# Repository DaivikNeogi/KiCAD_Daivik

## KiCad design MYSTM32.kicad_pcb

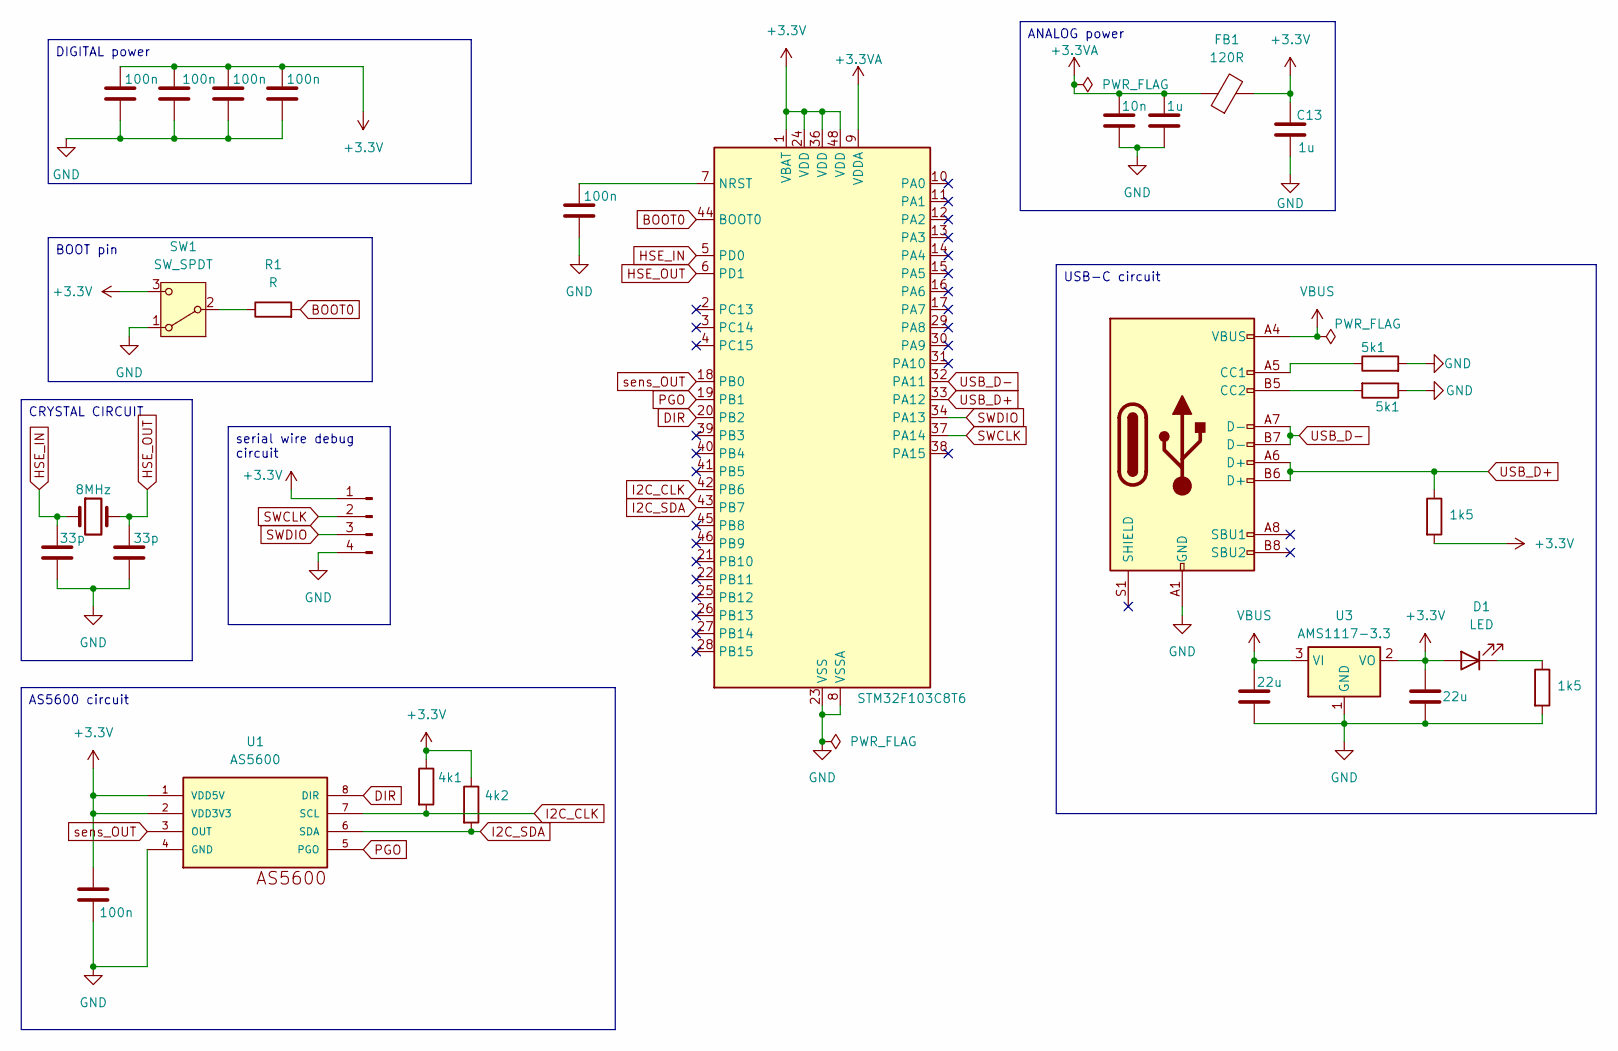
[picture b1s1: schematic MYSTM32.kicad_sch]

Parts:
4k1, 4k2: R; R_0603_1608Metric
C1, C2: 33p; C_0603_1608Metric
C4, C5, C6, C7, C8: 100n; C_0603_1608Metric
C9: 10n; C_0603_1608Metric
C10, C13: 1u; C_0603_1608Metric
C11, C12: 22u; C_0603_1608Metric
D1: LED; LED_0603_1608Metric
FB1: 120R; BEADC1608X95N
J1: Conn_01x04_Pin; FanPinHeader_1x04_P2.54mm_Vertical
J2: USB_C_Receptacle_USB2.0_16P; USB_C_Receptacle_GCT_USB4105-xx-A_16P_TopMnt_Horizontal
R1: R; R_0603_1608Metric
R2, R3: 5k1; R_0603_1608Metric
R4, R5: 1k5; R_0603_1608Metric
SW1: SW_SPDT; SW_SPDT_CK_JS102011SAQN
U1: AS5600; SOIC8
U2: STM32F103C8T6; LQFP-48_7x7mm_P0.5mm
U3: AMS1117-3.3; SOT-223-3_TabPin2
Y1: 8MHz; Crystal_SMD_0603-2Pin_6.0x3.5mm
buffer c1: 100n; C_0603_1608Metric

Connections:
+3.3V: 4k1.1, 4k2.1, C4.1, C5.1, C6.1, C7.1, C12.1, C13.1, D1.2 (A), FB1.2, J1.1, R4.2, SW1.3 (C), U1.1 (VDD5V), U1.2 (VDD3V3), U2.1 (VBAT), U2.24 (VDD), U2.36 (VDD), U2.48 (VDD), U3.2 (VO), buffer c1.1
+3.3VA: C9.1, C10.1, FB1.1, U2.9 (VDDA)
BOOT0: R1.2, U2.44 (BOOT0)
DIR: U1.8 (DIR), U2.20 (PB2)
GND: C1.2, C2.2, C4.2, C5.2, C6.2, C7.2, C8.2, C9.2, C10.2, C11.2, C12.2, C13.2, J1.4, J2.A1 (GND), J2.A12 (GND), J2.B1 (GND), J2.B12 (GND), R2.2, R3.1, R5.2, SW1.1 (A), U1.4 (GND), U2.8 (VSSA), U2.23 (VSS), U2.35 (VSS), U2.47 (VSS), U3.1 (GND), buffer c1.2
HSE_IN: C1.1, U2.5 (PD0), Y1.1
HSE_OUT: C2.1, U2.6 (PD1), Y1.2
I2C_CLK: 4k1.2, U1.7 (SCL), U2.42 (PB6)
I2C_SDA: 4k2.2, U1.6 (SDA), U2.43 (PB7)
unnamed: D1.1 (K), R5.1
unnamed: J2.A5 (CC1), R2.1
unnamed: J2.B5 (CC2), R3.2
unnamed: R1.1, SW1.2 (B)
unnamed: C8.1, U2.7 (NRST)
PGO: U1.5 (PGO), U2.19 (PB1)
SWCLK: J1.2, U2.37 (PA14)
SWDIO: J1.3, U2.34 (PA13)
USB_D+: J2.A6 (D+), J2.B6 (D+), R4.1, U2.33 (PA12)
USB_D-: J2.A7 (D-), J2.B7 (D-), U2.32 (PA11)
VBUS: C11.1, J2.A4 (VBUS), J2.A9 (VBUS), J2.B4 (VBUS), J2.B9 (VBUS), U3.3 (VI)
sens_OUT: U1.3 (OUT), U2.18 (PB0)

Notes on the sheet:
ANALOG power
AS5600 circuit
CRYSTAL CIRCUIT
DIGITAL power
serial wire debug circuit
USB-C circuit
BOOT pin

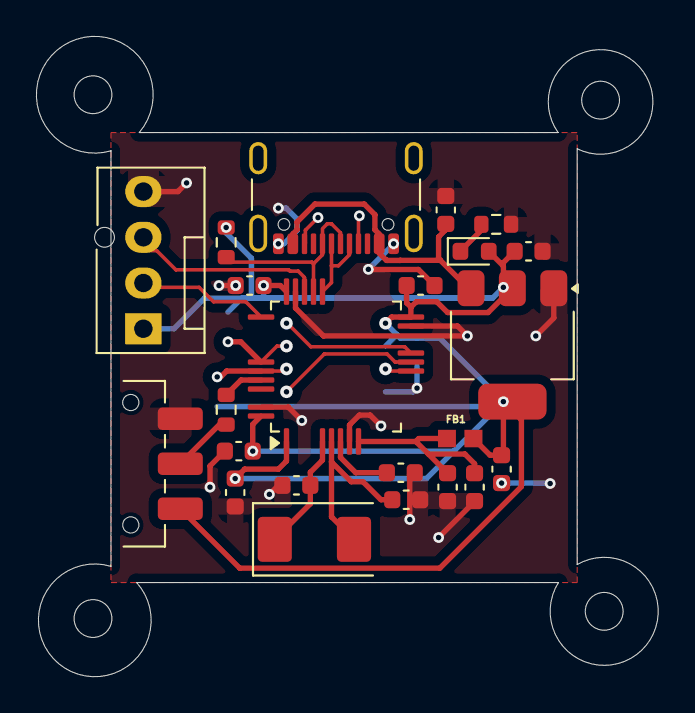
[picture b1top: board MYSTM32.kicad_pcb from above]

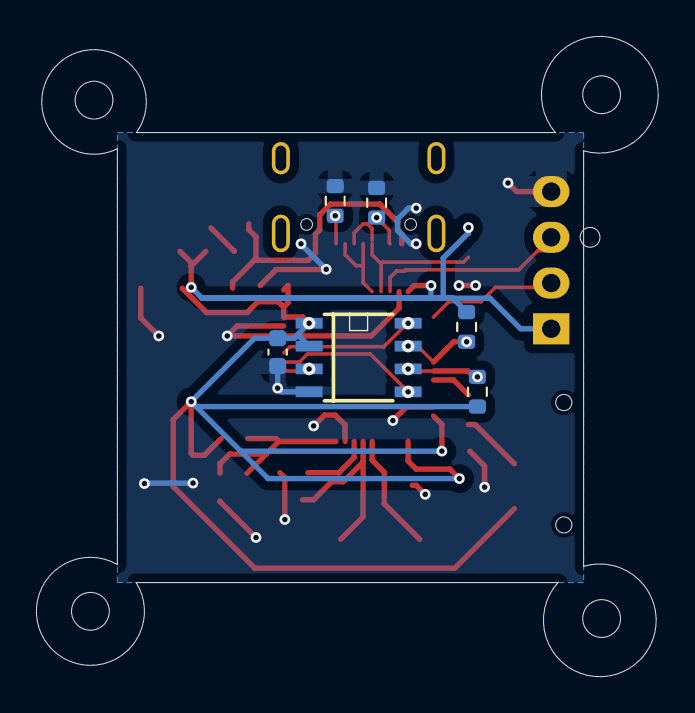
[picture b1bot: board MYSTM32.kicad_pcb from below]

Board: 2 copper layers, 34.5 x 35.6 mm, 29 parts (6 on the bottom side), 21 nets.
